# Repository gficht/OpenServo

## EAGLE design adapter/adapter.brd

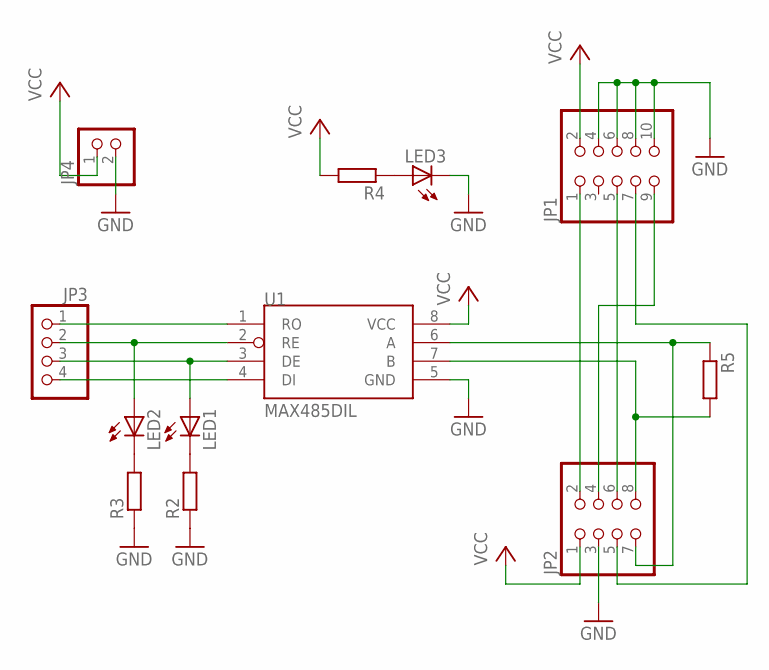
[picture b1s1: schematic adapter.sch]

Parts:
JP1: PINHD-2X5; 2X05
JP2: PINHD-2X4; 2X04
JP3: PINHD-1X4; 1X04
JP4: PINHD-1X2; 1X02
LED1, LED2, LED3: LEDCHIPLED_0805; CHIPLED_0805
R2, R3, R4, R5: R-EU_R0805; R0805
U1: MAX485DIL; DIL08

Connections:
A: JP2.7, R5.1, U1.6 (A)
B: JP2.8, R5.2, U1.7 (B)
GND: JP1.4, JP1.6, JP1.8, JP1.10, JP2.3, JP4.2, LED3.C, R2.1, R3.1, U1.5 (GND)
MISO: JP1.9, JP2.4
MOSI: JP1.1, JP2.2
unnamed: JP3.1, U1.1 (RO)
unnamed: JP3.2, LED2.A, U1.2 (RE)
unnamed: JP3.3, LED1.A, U1.3 (DE)
unnamed: JP3.4, U1.4 (DI)
unnamed: LED2.C, R3.2
unnamed: LED1.C, R2.2
unnamed: LED3.A, R4.1
RST: JP1.5, JP2.6
SCK: JP1.7, JP2.5
VCC: JP1.2, JP2.1, JP4.1, R4.2, U1.8 (VCC)

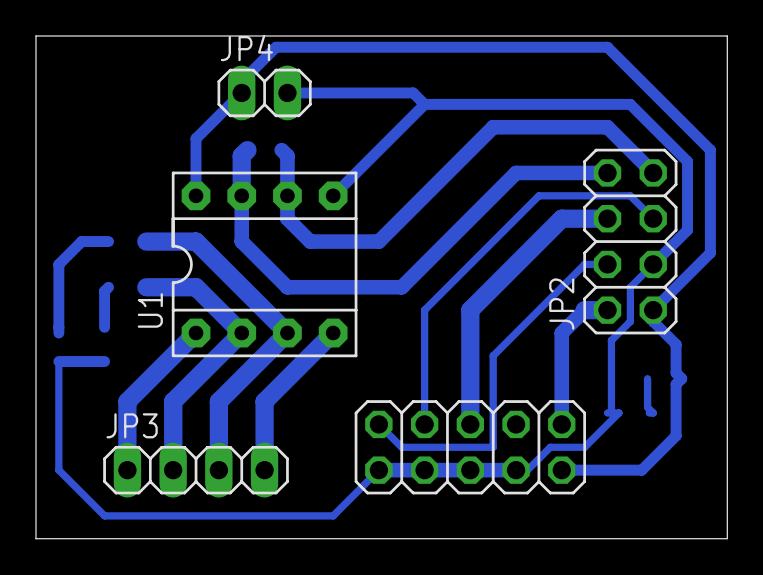
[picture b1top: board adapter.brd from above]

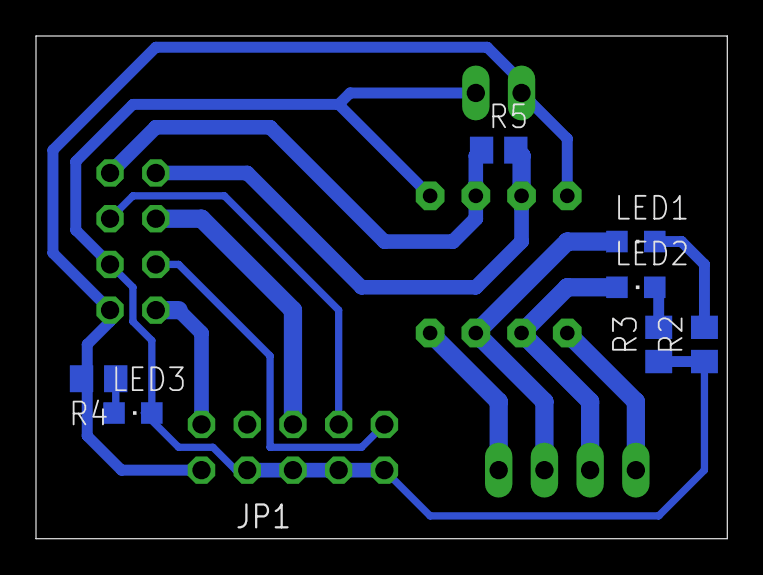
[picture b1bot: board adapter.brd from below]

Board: 2 copper layers, 38.4 x 27.9 mm, 12 parts (7 on the bottom side), 15 nets.

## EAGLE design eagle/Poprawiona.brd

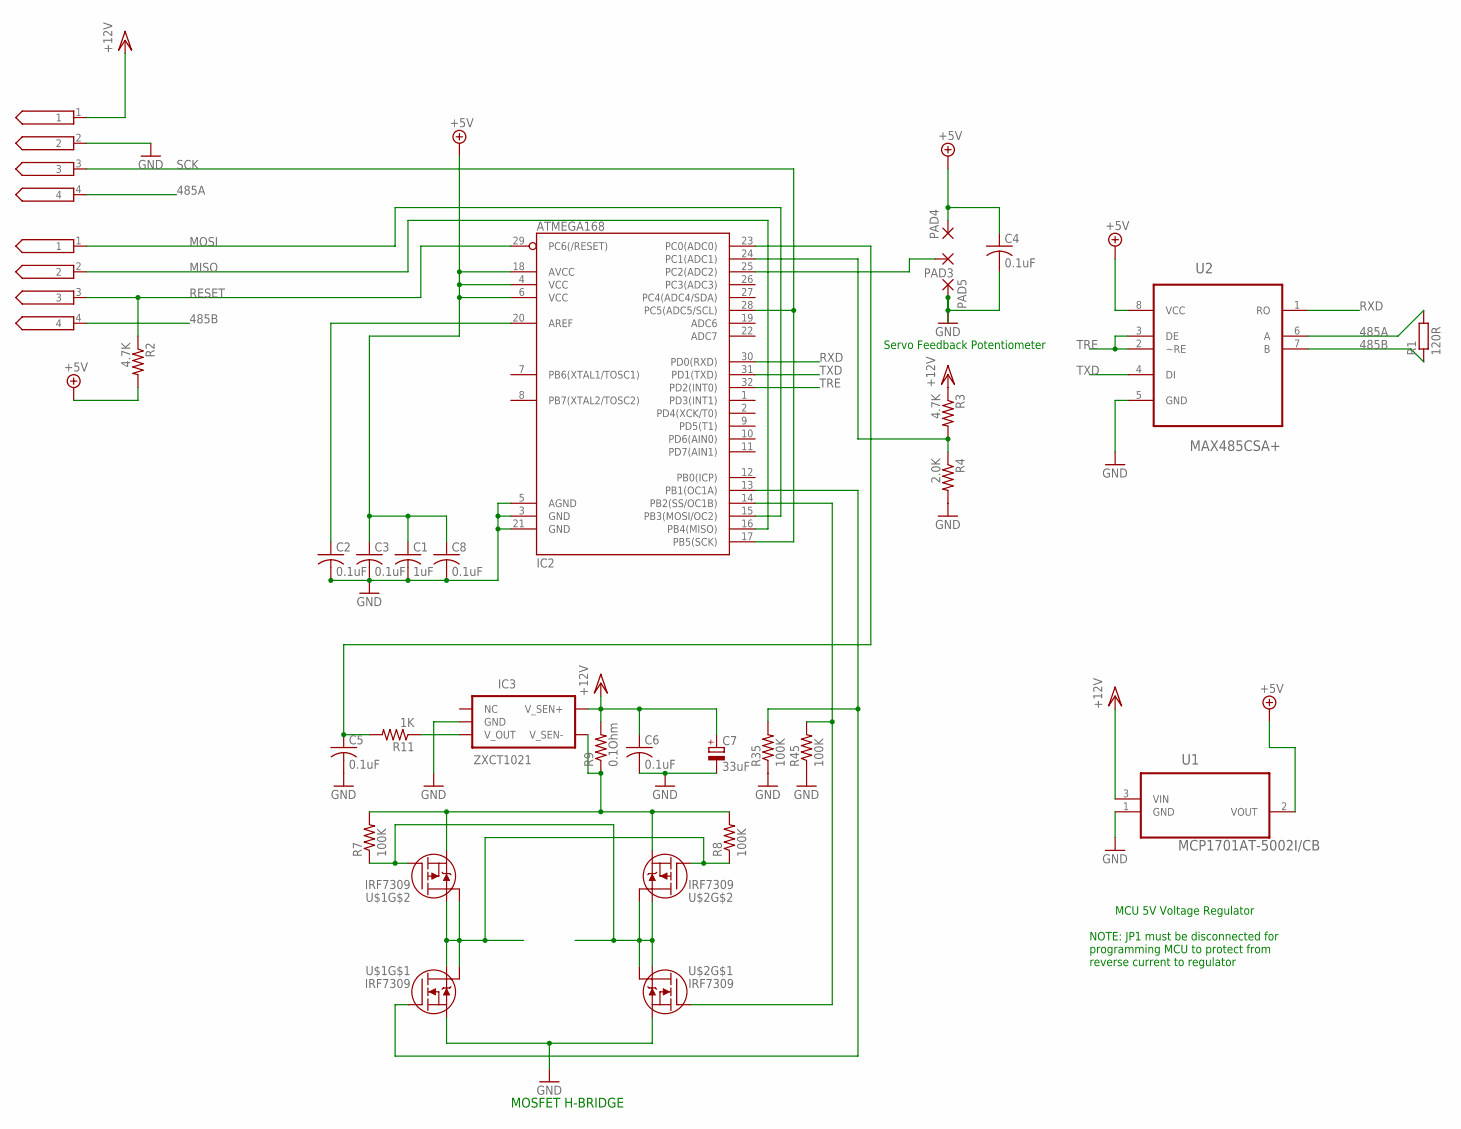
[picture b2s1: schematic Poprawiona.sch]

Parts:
C1: 1uF; C0603
C2, C3, C4, C6, C8: 0.1uF; C0603
C5: 0.1uF; C0603K
C7: 33uF; B/3528-21R
IC2: ATMEGA168; TQFP32-08
IC3: ZXCT1021; SOT23-5
JP1, JP2: 4-EDGEVERSION2; 4-PIN-EDGE-V2
PAD3, PAD4, PAD5: 1,6/0,8
R1: 120R; R0603
R2, R3: 4.7K; R0603
R4: 2.0K; R0603
R7, R8, R35, R45: 100K; R0603
R9: 0.1Ohm; R0603
R11: 1K; R0603
U1: MCP1701AT-5002I/CB; SOT95P255X145-3N
U2: MAX485CSA+; SOIC127P600X175-8N
U$1, U$2: IRF7309; SO8-2

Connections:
485A: JP1.4, R1.2, U2.6 (A)
485B: JP2.4, R1.1, U2.7 (B)
+5V: C1.1, C3.1, C4.1, C8.1, IC2.4 (VCC), IC2.6 (VCC), IC2.18 (AVCC), PAD4.1, R2.2, U1.2 (VOUT), U2.8 (VCC)
CURRENT: C5.1, IC2.23 (PC0(ADC0)), R11.2
GND: C1.2, C2.2, C3.2, C4.2, C5.2, C6.2, C7.-, C8.2, IC2.3 (GND), IC2.5 (AGND), IC2.21 (GND), IC3.2 (GND), JP1.2, PAD5.1, R4.2, R35.1, R45.1, U1.1 (GND), U2.5 (GND), U$1.1 (S), U$2.1 (S)
MISO: IC2.16 (PB4(MISO)), JP2.2
MOSI: IC2.15 (PB3(MOSI/OC2)), JP2.1
unnamed: R7.1, U$1.4 (G), U$2.5 (D), U$2.6 (D), U$2.7 (D), U$2.8 (D)
unnamed: IC3.3 (V_OUT), R11.1
unnamed: IC3.5 (V_SEN-), R7.2, R8.2, R9.1, U$1.3 (S), U$2.3 (S)
unnamed: IC2.14 (PB2(SS/OC1B)), R45.2, U$2.2 (G)
unnamed: IC2.25 (PC2(ADC2)), PAD3.1
unnamed: IC2.13 (PB1(OC1A)), R35.2, U$1.2 (G)
unnamed: C2.1, IC2.20 (AREF)
unnamed: IC2.24 (PC1(ADC1)), R3.2, R4.1
unnamed: R8.1, U$1.5 (D), U$1.6 (D), U$1.7 (D), U$1.8 (D), U$2.4 (G)
RESET: IC2.29 (PC6(/RESET)), JP2.3, R2.1
RXD: IC2.30 (PD0(RXD)), U2.1 (RO)
SCK: IC2.17 (PB5(SCK)), IC2.28 (PC5(ADC5/SCL)), JP1.3
TRE: IC2.32 (PD2(INT0)), U2.2 (~RE), U2.3 (DE)
TXD: IC2.31 (PD1(TXD)), U2.4 (DI)
VCC/2: C6.1, C7.+, IC3.4 (V_SEN+), JP1.1, R3.1, R9.2, U1.3 (VIN)

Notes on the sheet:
MOSFET H-BRIDGE
MCU 5V Voltage Regulator
NOTE: JP1 must be disconnected for
programming MCU to protect from
reverse current to regulator
Servo Feedback Potentiometer

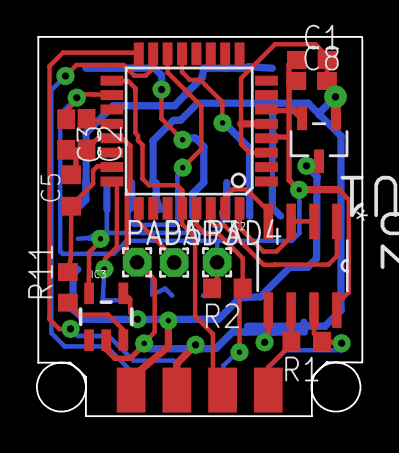
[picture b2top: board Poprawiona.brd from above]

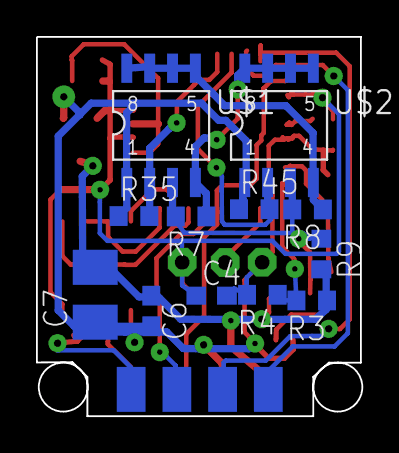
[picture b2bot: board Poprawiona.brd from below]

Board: 2 copper layers, 18.0 x 21.1 mm, 29 parts (13 on the bottom side), 22 nets.

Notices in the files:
parts and their libraries:
SparkFun: Licensing: CC v3.0 Share-Alike You are welcome to use this library for commercial purposes.
